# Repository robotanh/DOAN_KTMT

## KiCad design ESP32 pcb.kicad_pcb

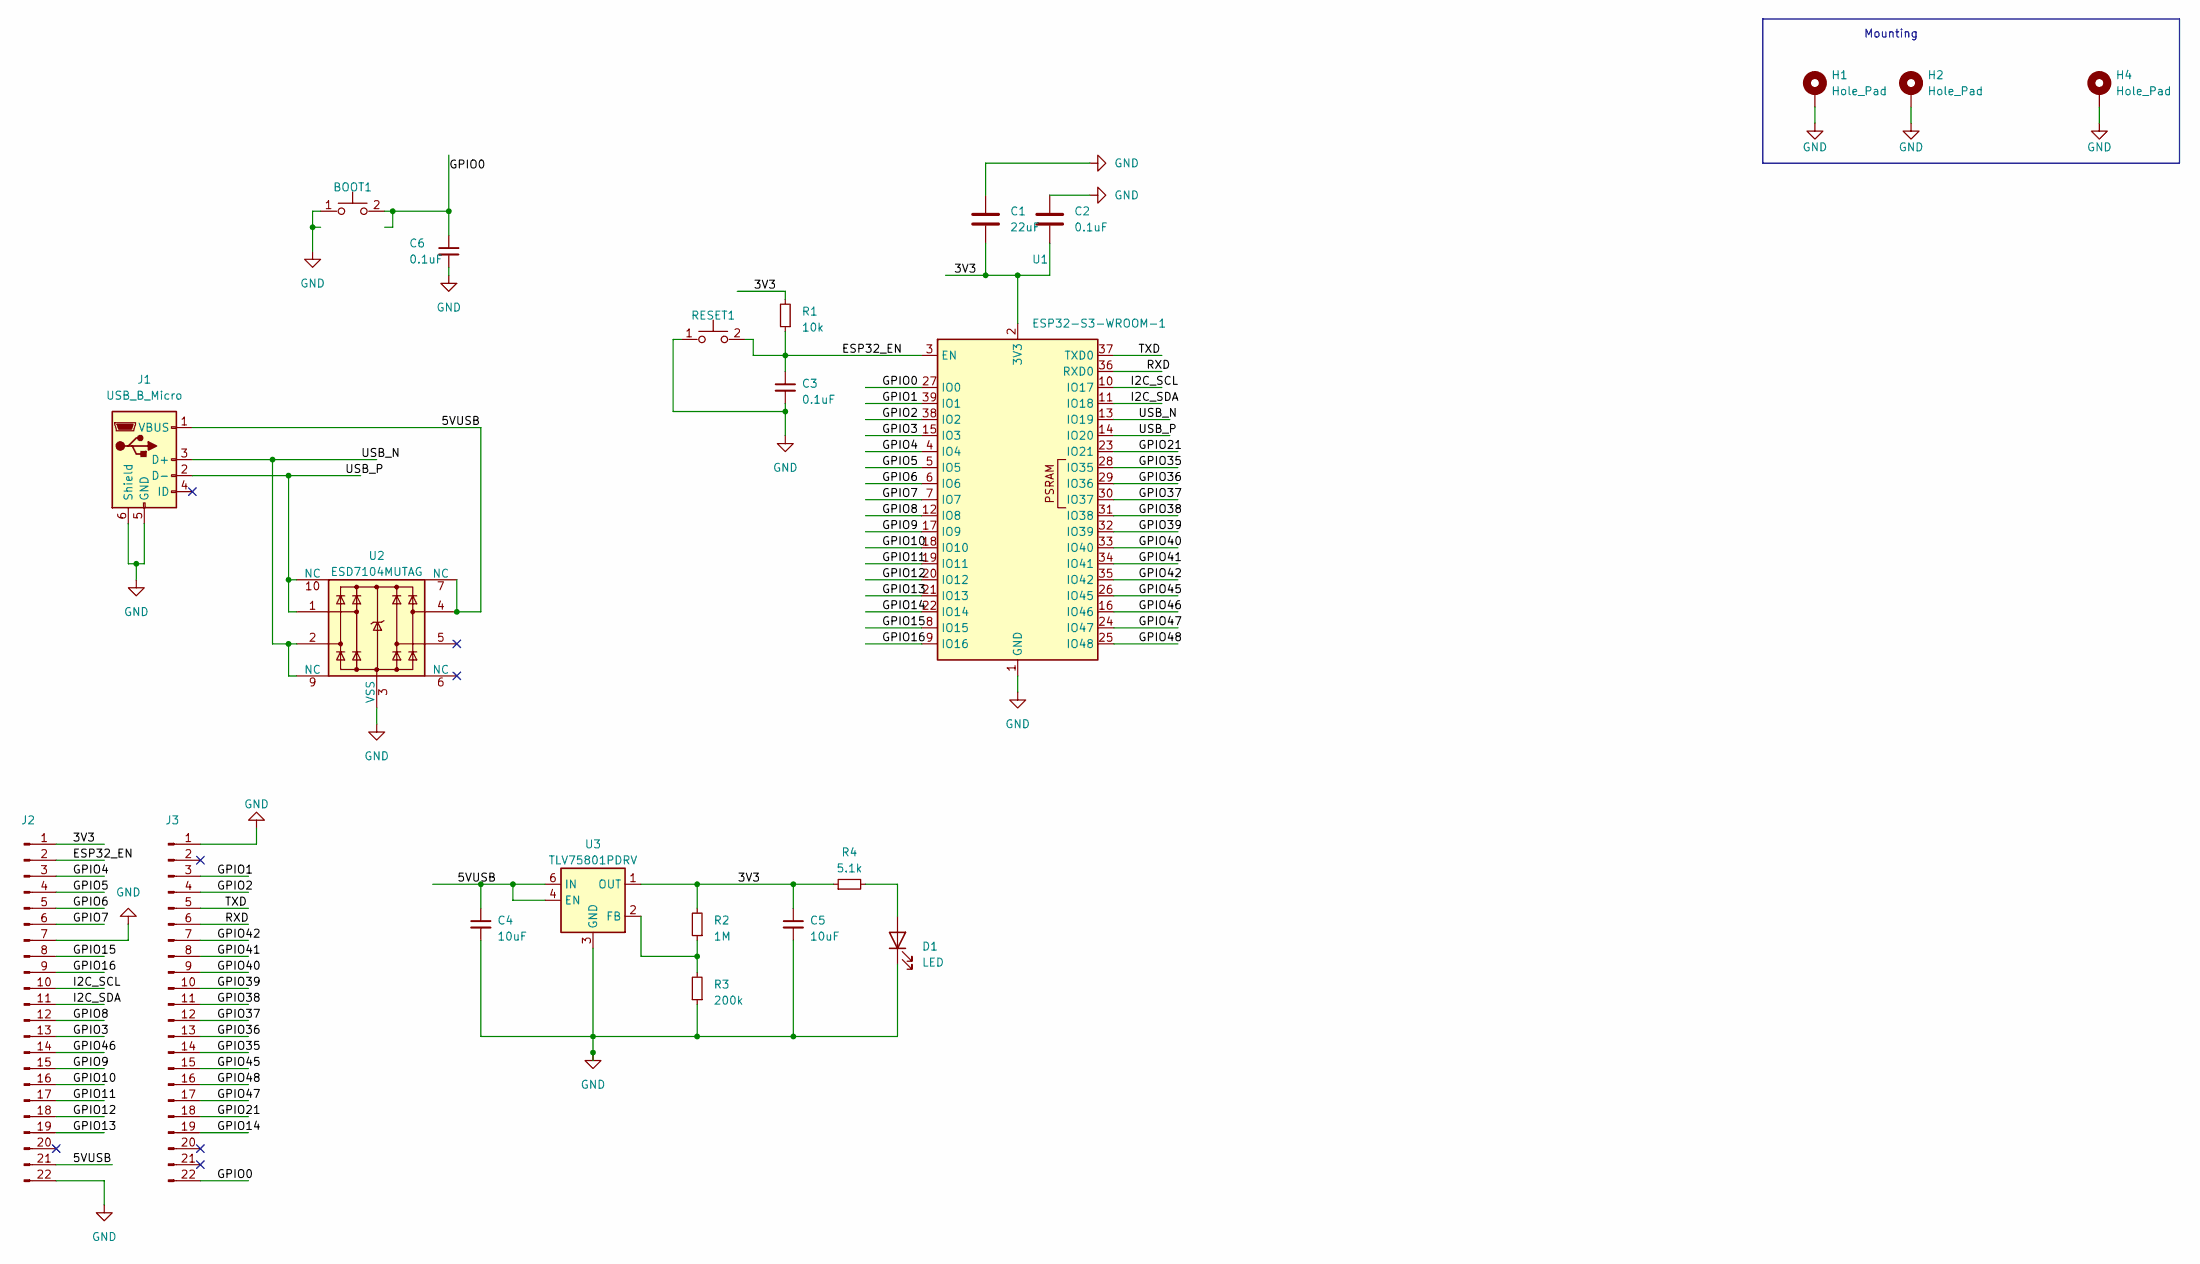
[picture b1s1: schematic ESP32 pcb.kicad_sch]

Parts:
BOOT1: SW_MEC_5GTH9
C1: 22uF; C_Axial_L3.8mm_D2.6mm_P7.50mm_Horizontal
C2, C3, C6: 0.1uF; C_Axial_L3.8mm_D2.6mm_P7.50mm_Horizontal
C4, C5: 10uF; C_Axial_L3.8mm_D2.6mm_P7.50mm_Horizontal
D1: LED; LED_D1.8mm_W1.8mm_H2.4mm_Horizontal_O1.27mm_Z1.6mm
H1, H2, H4: Hole_Pad; MountingHole_3.2mm_M3_Pad_Via
J1: USB_B_Micro; USB_Micro-B_Molex-105017-0001
J2, J3: PinHeader_1x22_P2.54mm_Vertical
R1: 10k; R_Axial_DIN0204_L3.6mm_D1.6mm_P5.08mm_Horizontal
R2: 1M; R_Axial_DIN0204_L3.6mm_D1.6mm_P5.08mm_Horizontal
R3: 200k; R_Axial_DIN0204_L3.6mm_D1.6mm_P5.08mm_Horizontal
R4: 5.1k; R_Axial_DIN0204_L3.6mm_D1.6mm_P5.08mm_Horizontal
RESET1: SW_MEC_5GTH9
U1: ESP32-S3-WROOM-1
U2: ESD7104MUTAG; Diodes_UDFN-10_1.0x2.5mm_P0.5mm
U3: TLV75801PDRV; WSON-6-1EP_2x2mm_P0.65mm_EP1x1.6mm

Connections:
/3V3: C1.2, C2.2, C5.1, J2.1, R1.2, R2.2, R4.1, U1.2 (3V3), U3.1 (OUT)
/5VUSB: C4.1, J1.1 (VBUS), J2.21, U2.4, U2.7 (NC), U3.4 (EN), U3.6 (IN)
/ESP32_EN: C3.1, J2.2, R1.1, RESET1.2 (A), U1.3 (EN)
/GPIO0: BOOT1.2 (A), C6.1, J3.22, U1.27 (IO0)
/GPIO1: J3.3, U1.39 (IO1)
/GPIO2: J3.4, U1.38 (IO2)
/GPIO3: J2.13, U1.15 (IO3)
/GPIO4: J2.3, U1.4 (IO4)
/GPIO5: J2.4, U1.5 (IO5)
/GPIO6: J2.5, U1.6 (IO6)
/GPIO7: J2.6, U1.7 (IO7)
/GPIO8: J2.12, U1.12 (IO8)
/GPIO9: J2.15, U1.17 (IO9)
/GPIO10: J2.16, U1.18 (IO10)
/GPIO11: J2.17, U1.19 (IO11)
/GPIO12: J2.18, U1.20 (IO12)
/GPIO13: J2.19, U1.21 (IO13)
/GPIO14: J3.19, U1.22 (IO14)
/GPIO15: J2.8, U1.8 (IO15)
/GPIO16: J2.9, U1.9 (IO16)
/GPIO21: J3.18, U1.23 (IO21)
/GPIO35: J3.14, U1.28 (IO35)
/GPIO36: J3.13, U1.29 (IO36)
/GPIO37: J3.12, U1.30 (IO37)
/GPIO38: J3.11, U1.31 (IO38)
/GPIO39: J3.10, U1.32 (IO39)
/GPIO40: J3.9, U1.33 (IO40)
/GPIO41: J3.8, U1.34 (IO41)
/GPIO42: J3.7, U1.35 (IO42)
/GPIO45: J3.15, U1.26 (IO45)
/GPIO46: J2.14, U1.16 (IO46)
/GPIO47: J3.17, U1.24 (IO47)
/GPIO48: J3.16, U1.25 (IO48)
/I2C_SCL: J2.10, U1.10 (IO17)
/I2C_SDA: J2.11, U1.11 (IO18)
/RXD: J3.6, U1.36 (RXD0)
/TXD: J3.5, U1.37 (TXD0)
/USB_N: J1.3 (D+), U1.13 (IO19), U2.2, U2.9 (NC)
/USB_P: J1.2 (D-), U1.14 (IO20), U2.1, U2.10 (NC)
GND: BOOT1.1, C1.1, C2.1, C3.2, C4.2, C5.2, C6.2, D1.1 (K), H1.1, H2.1, H4.1, J1.5 (GND), J1.6 (Shield), J2.7, J2.22, J3.1, R3.1, RESET1.1, U1.1 (GND), U1.40 (GND), U1.41 (GND), U2.3 (VSS), U2.8 (VSS), U3.3 (GND), U3.7 (GND)
unnamed: D1.2 (A), R4.2
unnamed: R2.1, R3.2, U3.2 (FB)

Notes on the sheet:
Mounting

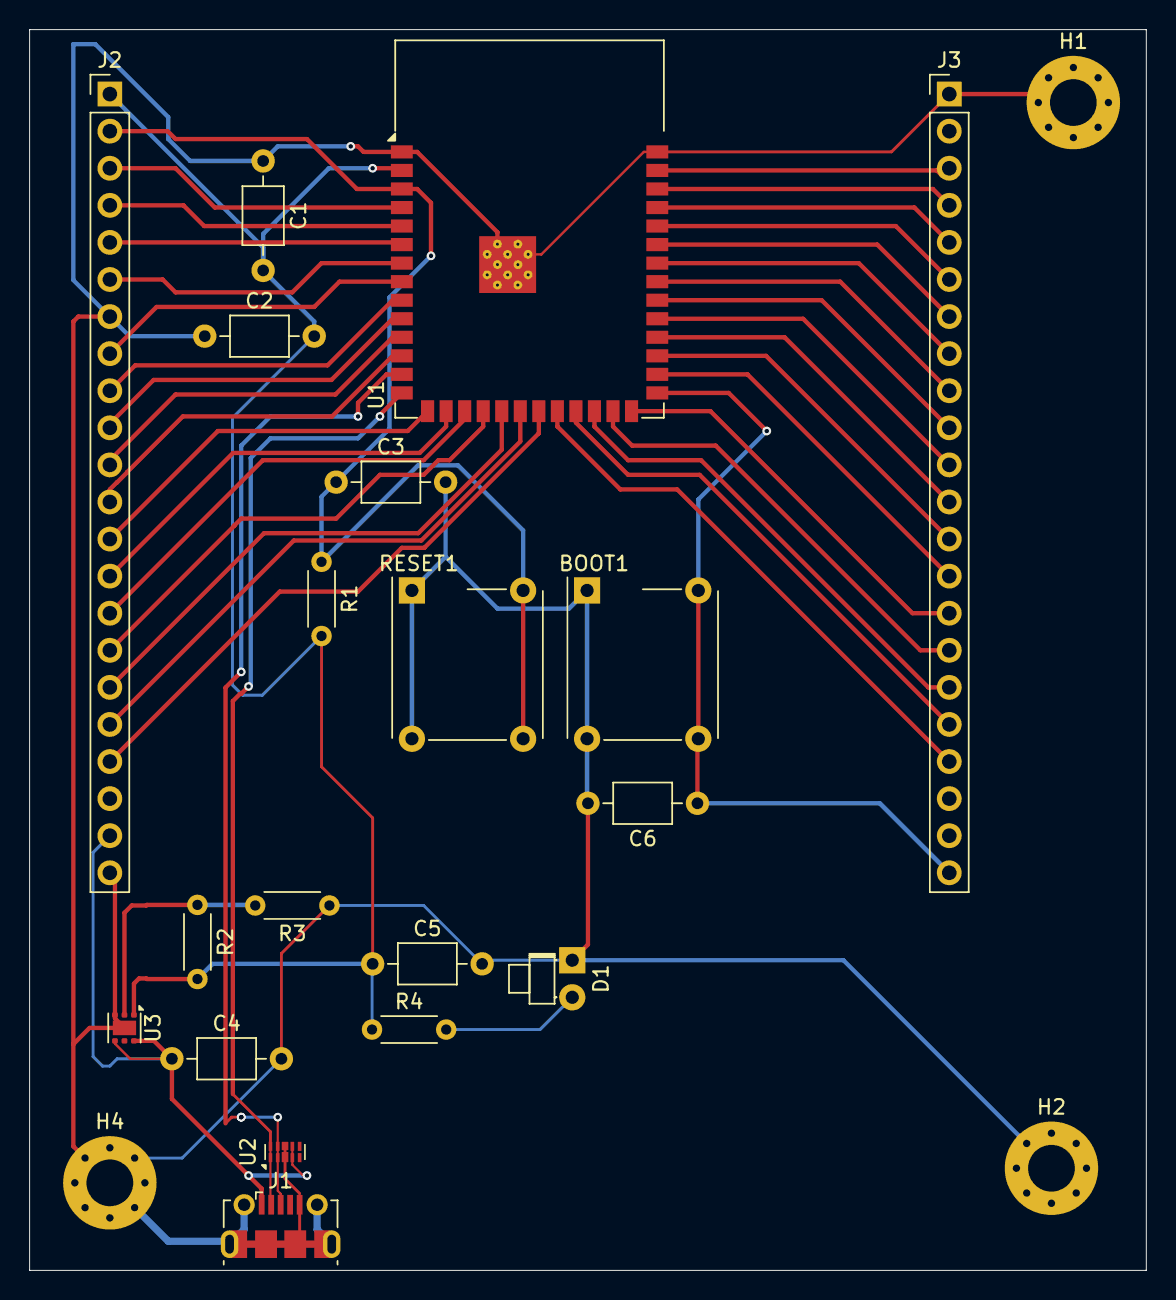
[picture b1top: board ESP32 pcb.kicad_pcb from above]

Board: 2 copper layers, 76.5 x 85.0 mm, 22 parts (0 on the bottom side), 42 nets.
